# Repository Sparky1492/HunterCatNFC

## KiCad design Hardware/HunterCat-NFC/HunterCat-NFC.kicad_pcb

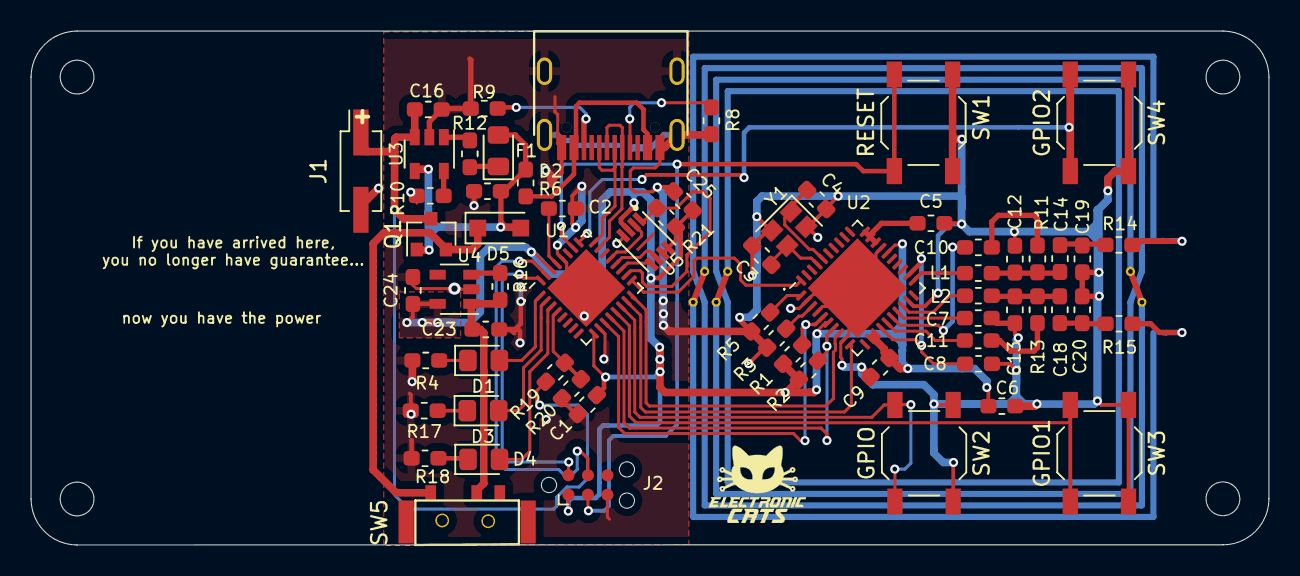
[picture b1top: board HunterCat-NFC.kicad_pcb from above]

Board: 2 copper layers, 80.7 x 33.5 mm, 69 parts (1 on the bottom side), 57 nets.

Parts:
C1, C25: 0.1uF; C_0603_1608Metric_Pad1.05x0.95mm_HandSolder
C2, C5, C6, C8: 1uF; C_0603_1608Metric_Pad1.05x0.95mm_HandSolder
C3, C4: 10pF; C_0603_1608Metric_Pad1.05x0.95mm_HandSolder
C7, C9: 100nF; C_0603_1608Metric_Pad1.05x0.95mm_HandSolder
C10, C11: 1nF/16V; C_0603_1608Metric_Pad1.05x0.95mm_HandSolder
C12, C13: 680pF; C_0603_1608Metric_Pad1.05x0.95mm_HandSolder
C14, C18: 100pF/50V; C_0603_1608Metric_Pad1.05x0.95mm_HandSolder
C16, C23, C24: 10uF; C_0603_1608Metric_Pad1.05x0.95mm_HandSolder
C19, C20: 120pF; C_0603_1608Metric_Pad1.05x0.95mm_HandSolder
D1, D2, D3, D4: LED; LED_0805_2012Metric_Pad1.15x1.40mm_HandSolder
D5: MBR120; D_SOD-123F
F1: 0.5A; Fuse_0603_1608Metric_Pad1.05x0.95mm_HandSolder
H1, H2, H3, H4: MountingHole; MountingHole_2.2mm_M2
J1: Battery; PinSocket_2x01_P2.54mm_Vertical_SMD
J2: Conn_01x06_Female; Tag-Connect_TC2030-IDC-NL_2x03_P1.27mm_Vertical
L1, L2: 160nH; L_0603_1608Metric_Pad1.05x0.95mm_HandSolder
L3: L; NFC-antenna30.4x30.4mm
P1: USB_C_Plug_USB2.0; C393939
Q1: DMG3415U-7; SOT-23
R1, R2, R16, R21: 10K; R_0603_1608Metric_Pad1.05x0.95mm_HandSolder
R3, R5, R6, R19, R20: 100K; R_0603_1608Metric_Pad1.05x0.95mm_HandSolder
R4, R10, R12, R17, R18: 1K; R_0603_1608Metric_Pad1.05x0.95mm_HandSolder
R8, R9: 5k1; R_0603_1608Metric_Pad1.05x0.95mm_HandSolder
R11, R13: 2k2; R_0603_1608Metric_Pad1.05x0.95mm_HandSolder
R14, R15: 3.24R; R_0603_1608Metric_Pad1.05x0.95mm_HandSolder
SW1: RESET; SW_SPST_TL3342
SW2: GPIO; SW_SPST_TL3342
SW3: GPIO1; SW_SPST_TL3342
SW4: GPIO2; SW_SPST_TL3342
SW5: ON; Micro_interruptor_SPDT
U1: ATSAMD21E18A; QFN-32-1EP_5x5mm_P0.5mm_EP3.6x3.6mm
U2: PN7150B0HN_C11002E-PN7150B0HN_C11002E; QFN-40-1EP_6x6mm_P0.5mm_EP4.6x4.6mm
U3: MCP73831-3-OT; SOT-23-5
U4: AP2112K-3.3; SOT-23-5
U5: GD25Q16CEIGR; PSON50P200X300X50-9N
Y1: 27.12Mhz; Crystal_SMD_2520-4Pin_2.5x2.0mm

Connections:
+3V3: C1.1, C6.1, C9.1, C24.1, C25.1, J2.1, R1.1, R2.1, R21.1, U1.9, U1.30, U2.6, U2.12, U2.13, U2.26, U4.5, U5.3, U5.7, U5.8
+BATT: C16.1, J1.1, Q1.3, R19.1, U3.3
/ADR0: R5.1, U2.1
/ADR1: R3.1, U2.3
/B_ADC: R19.2, R20.1, U1.4
/CLK: U1.17, U2.40
/CS: R21.2, U1.18, U5.1
/D+: P1.A6, U1.24
/D-: P1.A7, U1.23
/GPIO: SW4.2, U1.25
/GPIO1: SW2.2, U1.14
/GPIO2: SW3.2, U1.13
/IRQ: U1.16, U2.8
/LED1: D1.2, U1.1
/LED2: D3.2, U1.2
/LED3: D4.2, U1.3
/MISO: U1.21, U5.2
/MOSI: U1.19, U5.5
/RST: J2.3, SW1.2, U1.26
/RXN: C11.2, U2.15
/RXP: C10.2, U2.16
/SCK: U1.20, U5.6
/SCL: R2.2, U1.12, U2.7
/SDA: R1.2, U1.11, U2.5
/SWCLK: J2.4, U1.31
/SWDIO: J2.2, U1.32
/TX1: L1.1, U2.21
/TX2: L2.2, U2.18
/VEN: U1.15, U2.10
GND: C1.2, C2.2, C3.2, C4.2, C5.2, C6.2, C7.2, C8.2, C9.2, C12.2, C13.1, C16.2, C19.2, C20.1, C23.2, C24.2, C25.2, J1.2, J2.5, P1.A1, R3.2, R4.2, R5.2, R6.2, R8.1, R9.1, R10.2, R17.2, R18.2, R20.2, SW1.1, SW2.1, SW3.1, SW4.1, U1.10, U1.28, U2.2, U2.4, U2.9, U2.19, U2.27, U2.41, U3.2, U4.2, U5.4, Y1.2, Y1.4
unnamed: C2.1, U1.29
unnamed: C3.1, U2.37, Y1.3
unnamed: C4.1, U2.36, Y1.1
unnamed: C5.1, U2.28, U2.29, U2.30
unnamed: C7.1, U2.17
unnamed: C8.1, U2.14, U2.22
unnamed: C10.1, R11.1
unnamed: C11.1, R13.2
unnamed: C12.1, C14.2, L1.2, R11.2
unnamed: C13.2, C18.2, L2.1, R13.1
unnamed: C14.1, C19.1, R14.2
unnamed: C18.1, C20.2, R15.2
unnamed: C23.1, R16.1, SW5.2, U4.1
unnamed: D1.1, R4.1
unnamed: D2.1, R12.2
unnamed: D3.1, R17.1
unnamed: D4.1, R18.1
unnamed: D5.1, Q1.2, SW5.1
unnamed: F1.1, P1.A4
unnamed: L3.1, R14.1
unnamed: L3.2, R15.1
unnamed: P1.A5, R8.2
unnamed: P1.B5, R9.2
unnamed: R10.1, U3.5
unnamed: R12.1, U3.1
unnamed: R16.2, U4.3
VBUS: D2.2, D5.2, F1.2, Q1.1, R6.1, U3.4

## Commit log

2021-01-12 changed flash footprint dimensions
